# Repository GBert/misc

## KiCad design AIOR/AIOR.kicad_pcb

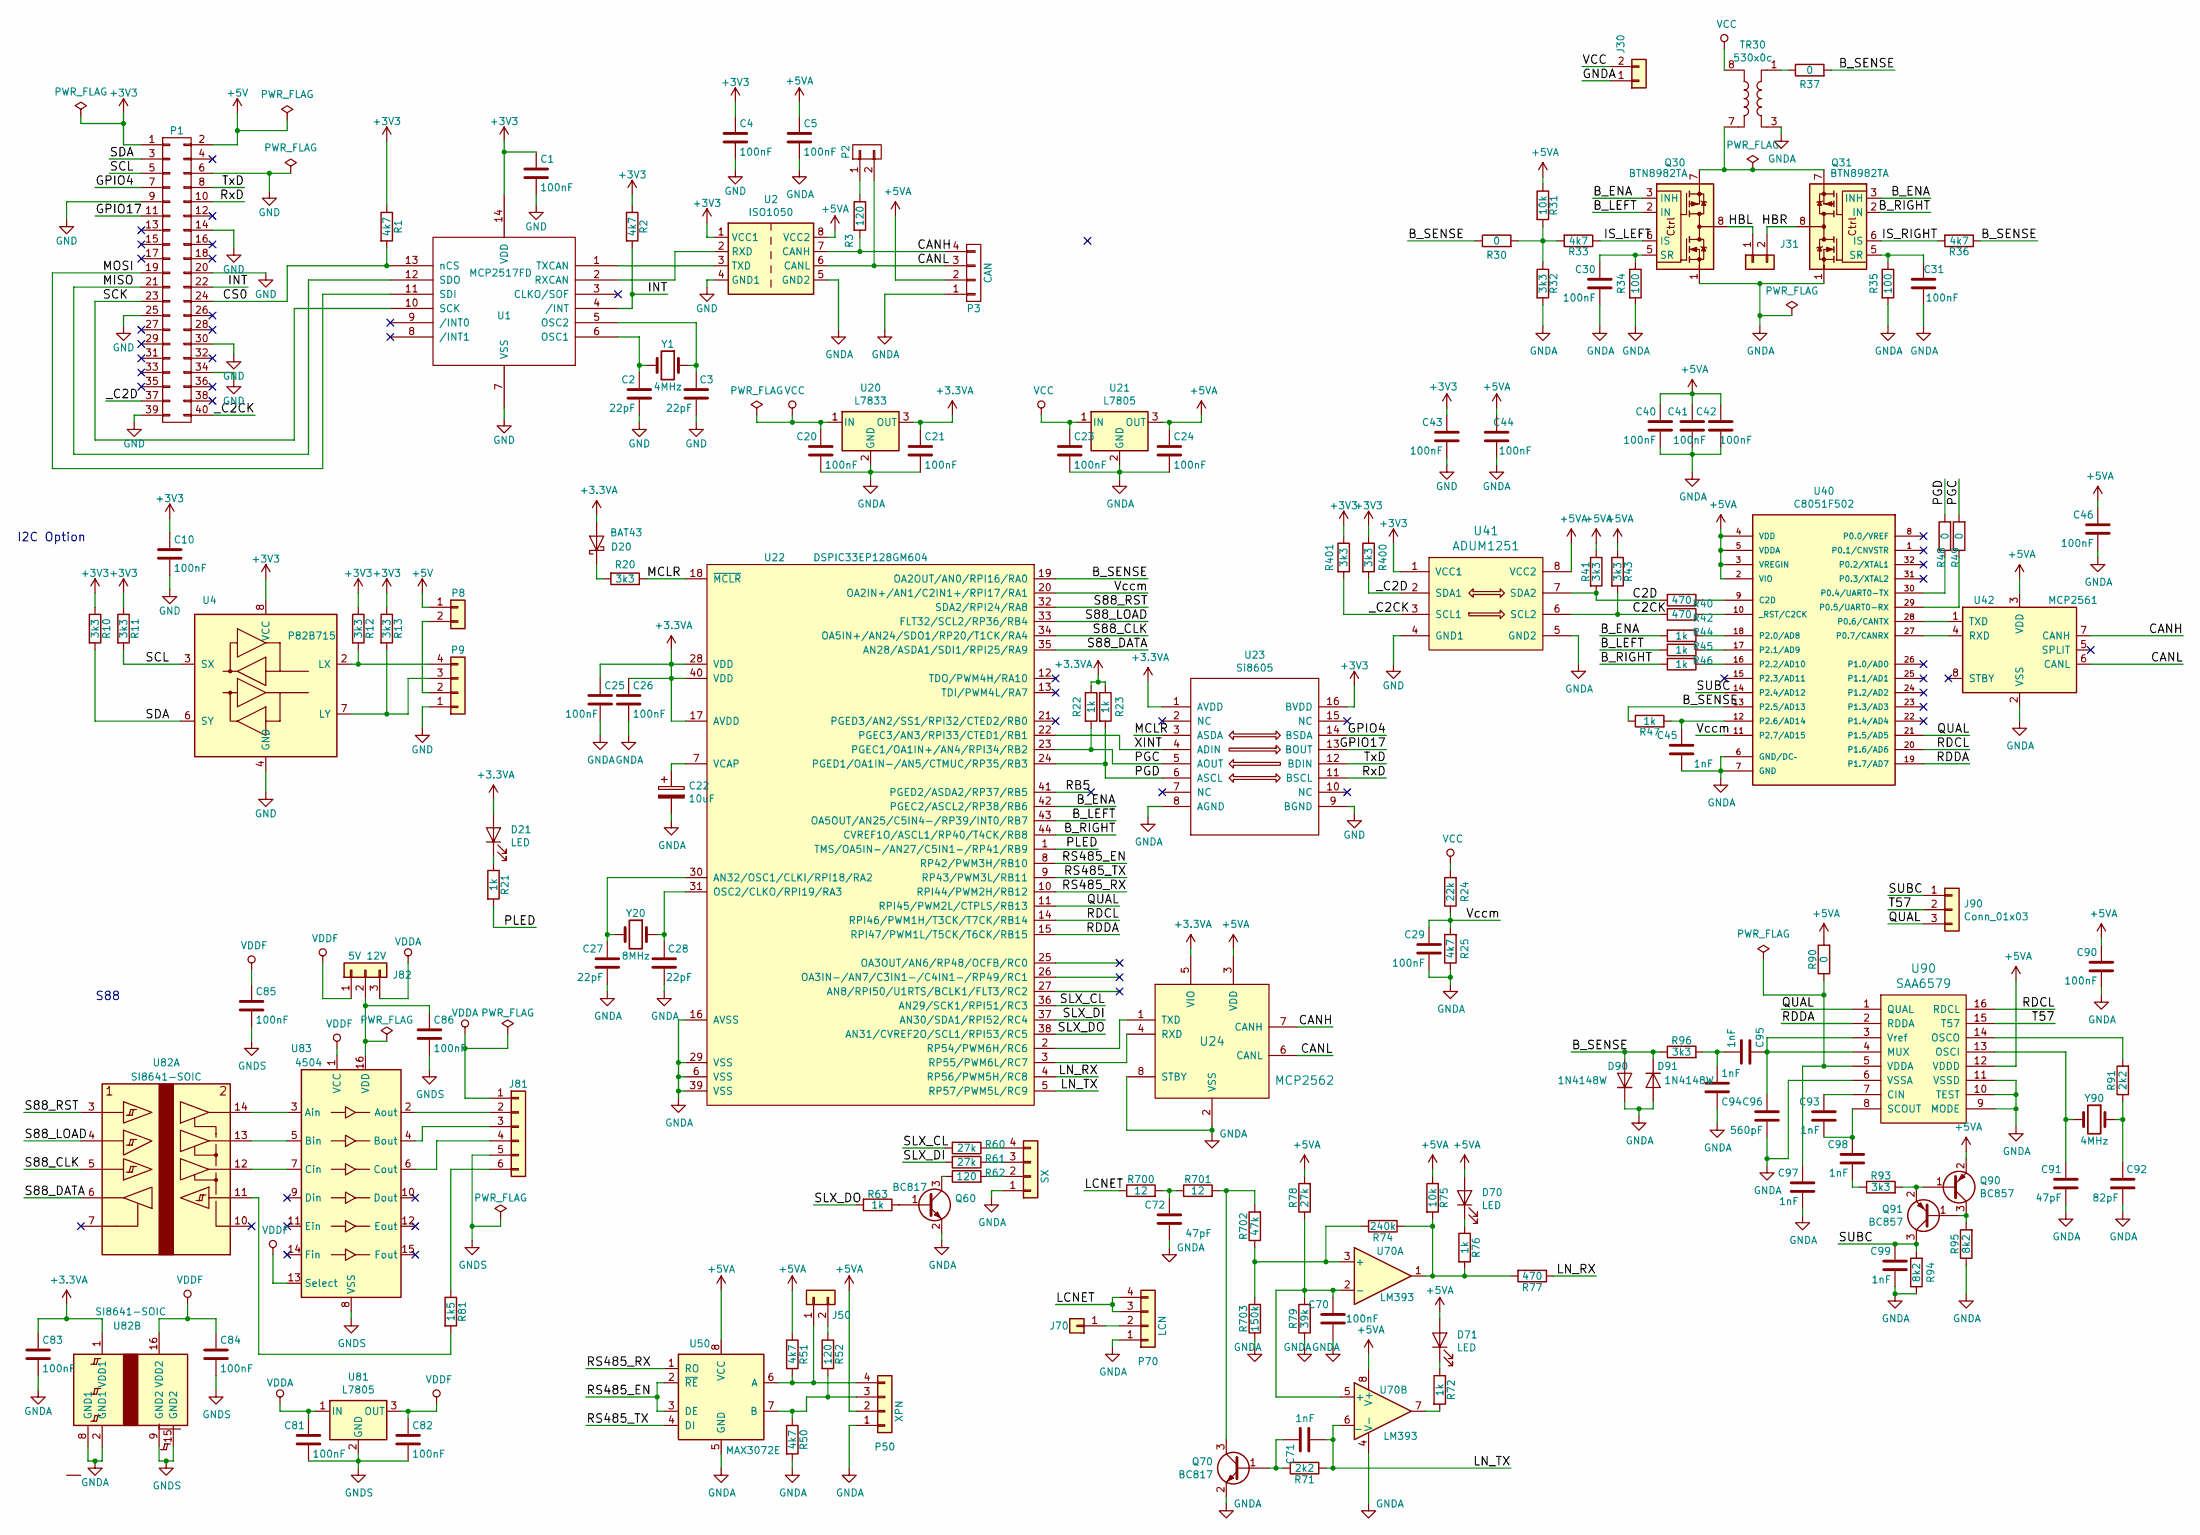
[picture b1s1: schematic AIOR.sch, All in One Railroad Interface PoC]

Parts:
C1, C4, C5, C10, C20, C21, C23, C24, C25, C26, C29, C30, C31, C40, C41, C42, C43, C44, C46, C70, C81, C82, C83, C84, C85, C86, C90: 100nF; C_0805_2012Metric_Pad1.15x1.40mm_HandSolder
C2, C3, C27, C28: 22pF; C_0805_2012Metric_Pad1.15x1.40mm_HandSolder
C22: 10uF; CP_EIA-6032-20_AVX-F_Pad2.25x2.35mm_HandSolder
C45, C71, C93, C94, C95, C97, C98, C99: 1nF; C_0805_2012Metric_Pad1.15x1.40mm_HandSolder
C72, C91: 47pF; C_0805_2012Metric_Pad1.15x1.40mm_HandSolder
C92: 82pF; C_0805_2012Metric_Pad1.15x1.40mm_HandSolder
C96: 560pF; C_0805_2012Metric_Pad1.15x1.40mm_HandSolder
D20: BAT43; D_SOD-323_HandSoldering
D21, D70, D71: LED; LED_0805_2012Metric_Pad1.15x1.40mm_HandSolder
D90, D91: 1N4148W; D_SOD-123
J30, J31: Conn_01x02; mkds_1,5-2
J50: Conn_01x02; PinHeader_1x02_P2.54mm_Vertical
J70: Conn_01x01; PinHeader_1x01_P2.54mm_Vertical
J81: S88; PinHeader_1x06_P2.54mm_Horizontal
J82: 5V 12V; PinHeader_1x03_P2.54mm_Vertical
J90: Conn_01x03; PinHeader_1x03_P2.54mm_Vertical
P1: CONN_02X20; Socket_Strip_Straight_2x20
P2: CONN_01X02; PinHeader_1x02_P2.54mm_Vertical
P3: CAN; b4b-ph-kl
P8: Conn_01x02; PinHeader_1x02_P2.54mm_Vertical
P9: Conn_01x04; s4b-ph-kl
P50: XPN; b4b-ph-kl
P60: SX; b4b-ph-kl
P70: LCN; b4b-ph-kl
Q30, Q31: BTN8982TA; TO-263-7_TabPin8
Q60, Q70: BC817; SOT-23_Handsoldering
Q90, Q91: BC857; SOT-23_Handsoldering
R1, R2, R25, R33, R36, R50, R51: 4k7; R_0805_2012Metric_Pad1.15x1.40mm_HandSolder
R3, R52: 120; R_1206_3216Metric_Pad1.42x1.75mm_HandSolder
R10, R11, R12, R13, R20, R32, R41, R43, R93, R96, R400, R401: 3k3; R_0805_2012Metric_Pad1.15x1.40mm_HandSolder
R21, R22, R23, R44, R45, R46, R47, R63, R72, R76: 1k; R_0805_2012Metric_Pad1.15x1.40mm_HandSolder
R24: 22k; R_0805_2012Metric_Pad1.15x1.40mm_HandSolder
R30, R37, R48, R49, R90: 0; R_0805_2012Metric_Pad1.15x1.40mm_HandSolder
R31, R75: 10k; R_0805_2012Metric_Pad1.15x1.40mm_HandSolder
R34, R35: 100; R_0805_2012Metric_Pad1.15x1.40mm_HandSolder
R40, R42, R77: 470; R_0805_2012Metric_Pad1.15x1.40mm_HandSolder
R60, R61, R78: 27k; R_0805_2012Metric_Pad1.15x1.40mm_HandSolder
R62: 120; R_0805_2012Metric_Pad1.15x1.40mm_HandSolder
R71, R91: 2k2; R_0805_2012Metric_Pad1.15x1.40mm_HandSolder
R74: 240k; R_0805_2012Metric_Pad1.15x1.40mm_HandSolder
R79: 39k; R_0805_2012Metric_Pad1.15x1.40mm_HandSolder
R81: 1k5; R_0805_2012Metric_Pad1.15x1.40mm_HandSolder
R94, R95: 8k2; R_0805_2012Metric_Pad1.15x1.40mm_HandSolder
R700, R701: 12; R_1206_3216Metric_Pad1.42x1.75mm_HandSolder
R702: 47k; R_0805_2012Metric_Pad1.15x1.40mm_HandSolder
R703: 150k; R_0805_2012Metric_Pad1.15x1.40mm_HandSolder
TR30: 530x0c; 530x0C
U1: MCP2517FD; so-14
U2: ISO1050; mdip_8
U4: P82B715; so-8
U20: L7833; TO-252-2
U21, U81: L7805; TO-252-2
U22: DSPIC33EP128GM604; LQFP-44_10x10mm_P0.8mm
U23: Si8605; so-16
U24: MCP2562; so-8
U40: C8051F502; LQFP-32_7x7mm_P0.8mm
U41: ADUM1251; so-8
U42: MCP2561; so-8
U50: MAX3072E; so-8
U70: LM393; so-8
U82: SI8641-SOIC; so-16
U83: 4504; so-16
U90: SAA6579; SOP-16_7.5x10.4mm_P1.27mm
Y1, Y90: 4MHz; crystal_hc-49s
Y20: 8MHz; crystal_hc-49s

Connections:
+3.3VA: C21.1, C25.1, C26.1, C83.1, D20.2 (A), D21.2 (A), R22.1, R23.1, U20.3 (OUT), U22.17 (AVDD), U22.28 (VDD), U22.40 (VDD), U23.1 (AVDD), U24.5 (VIO~), U82.1 (VDD1)
+3V3: C1.1, C4.1, C10.1, C43.1, P1.1, R1.1, R2.1, R10.1, R11.1, R12.1, R13.1, R400.1, R401.1, U1.14 (VDD), U2.1 (VCC1), U4.8 (VCC), U23.16 (BVDD), U41.1 (VCC1)
+5V: P1.2, P8.1
+5VA: C5.1, C24.1, C40.1, C41.1, C42.1, C44.1, C46.1, C90.1, D70.2 (A), D71.2 (A), P3.2, P50.2, Q90.2 (E), R31.1, R41.1, R43.1, R51.1, R75.1, R78.2, R90.2, U2.8 (VCC2), U21.3 (OUT), U24.3 (VDD~), U40.2 (VIO), U40.3 (VREGIN), U40.4 (VDD), U40.5 (VDDA), U41.8 (VCC2), U42.3 (VDD), U50.8 (VCC), U70.8 (V+), U90.12 (VDDD)
/B_ENA: Q30.3 (INH), Q31.3 (INH), R44.2, U22.42 (PGEC2/ASCL2/RP38/RB6)
/B_LEFT: Q30.2 (IN), R45.2, U22.43 (OA5OUT/AN25/C5IN4-/RP39/INT0/RB7)
/B_RIGHT: Q31.2 (IN), R46.2, U22.44 (CVREF1O/ASCL1/RP40/T4CK/RB8)
/B_SENSE: D90.2 (A), D91.1 (K), R30.1, R36.1, R37.2, R47.1, R96.1, U22.19 (OA2OUT/AN0/RPI16/RA0), U40.13 (P2.5/AD13)
/C2CK: R42.2, R43.2, U41.6 (SCL2)
/C2D: R40.2, R41.2, U41.7 (SDA2)
/CANH: P3.4, R3.2, U2.7 (CANH), U24.7 (CANH), U42.7 (CANH)
/CANL: P2.2, P3.3, U2.6 (CANL), U24.6 (CANL), U42.6 (CANL)
/CS0: P1.24, R1.2, U1.13 (nCS)
/GPIO4: P1.7, U23.14 (BSDA)
/GPIO17: P1.11, U23.13 (BOUT)
/HBL: J31.1, Q30.4, Q30.8
/HBR: J31.2, Q31.4, Q31.8
/INT: P1.22, R2.2, U1.4 (/INT)
/IS_LEFT: Q30.6 (IS), R33.1
/IS_RIGHT: Q31.6 (IS), R36.2
/LCNET: P70.3, P70.4, R700.1
/LN_RX: R77.1, U22.4 (RP56/PWM5H/RC8)
/LN_TX: C71.2, R71.1, U22.5 (RP57/PWM5L/RC9), U70.6 (_)
/MCLR: R20.1, U22.18 (~MCLR), U23.3 (ASDA)
/MISO: P1.21, U1.12 (SDO)
/MOSI: P1.19, U1.11 (SDI)
/PGC: R22.2, R49.2, U22.23 (PGEC1/OA1IN+/AN4/RPI34/RB2), U23.5 (AOUT)
/PGD: R23.2, R48.2, U22.24 (PGED1/OA1IN-/AN5/CTMUC/RP35/RB3), U23.6 (ASCL)
/PLED: R21.2, U22.1 (TMS/OA5IN-/AN27/C5IN1-/RP41/RB9)
/QUAL: J90.3, U22.11 (RPI45/PWM2L/CTPLS/RB13), U40.21 (P1.5/AD5), U90.1 (QUAL)
/RB5: U22.41 (PGED2/ASDA2/RP37/RB5)
/RDCL: U22.14 (RPI46/PWM1H/T3CK/T7CK/RB14), U40.20 (P1.6/AD6), U90.16 (RDCL)
/RDDA: U22.15 (RPI47/PWM1L/T5CK/T6CK/RB15), U40.19 (P1.7/AD7), U90.2 (RDDA)
/RS485_EN: U22.8 (RP42/PWM3H/RB10), U50.2 (~RE~), U50.3 (DE)
/RS485_RX: U22.10 (RPI44/PWM2H/RB12), U50.1 (RO)
/RS485_TX: U22.9 (RP43/PWM3L/RB11), U50.4 (DI)
/RxD: P1.10, U23.11 (BSCL)
/S88_CLK: U22.34 (OA5IN+/AN24/SDO1/RP20/T1CK/RA4), U82.5
/S88_DATA: U22.35 (AN28/ASDA1/SDI1/RPI25/RA9), U82.6
/S88_LOAD: U22.33 (FLT32/SCL2/RP36/RB4), U82.4
/S88_RST: U22.32 (SDA2/RPI24/RA8), U82.3
/SCK: P1.23, U1.10 (SCK)
/SCL: P1.5, R11.2, U4.3 (SX)
/SDA: P1.3, R10.2, U4.6 (SY)
/SLX_CL: R60.2, U22.36 (AN29/SCK1/RPI51/RC3)
/SLX_DI: R61.2, U22.37 (AN30/SDA1/RPI52/RC4)
/SLX_DO: R63.2, U22.38 (AN31/CVREF2O/SCL1/RPI53/RC5)
/SUBC: C99.1, J90.1, Q91.3 (C), R94.2, U40.14 (P2.4/AD12)
/T57: J90.2, U90.15 (T57)
/TxD: P1.8, U23.12 (BDIN)
/Vccm: C29.1, R24.1, R25.2, U22.20 (OA2IN+/AN1/C2IN1+/RPI17/RA1), U40.11 (P2.7/AD15)
/XINT: U22.22 (PGEC3/AN3/RPI33/CTED1/RB1), U23.4 (ADIN)
/_C2CK: P1.40, R401.2, U41.3 (SCL1)
/_C2D: P1.37, R400.2, U41.2 (SDA1)
GND: C1.2, C2.2, C3.2, C4.2, C10.2, C43.2, P1.6, P1.9, P1.14, P1.20, P1.25, P1.30, P1.34, P1.39, P9.1, U1.7 (VSS), U2.4 (GND1), U4.4 (GND), U23.9 (BGND), U41.4 (GND1)
GNDA: C5.2, C20.2, C21.2, C22.2, C23.2, C24.2, C25.2, C26.2, C27.2, C28.2, C29.2, C30.2, C31.2, C40.2, C41.2, C42.2, C44.2, C45.2, C46.2, C70.2, C72.2, C83.2, C90.2, C91.2, C92.2, C94.1, C96.2, C97.2, C99.2, D90.1 (K), D91.2 (A), J30.1, P3.1, P50.1, P60.1, P70.1, Q30.1, Q31.1, Q60.2 (E), Q70.2 (E), R25.1, R32.2, R34.2, R35.2, R50.2, R79.1, R94.1, R95.1, R703.1, TR30.3, U2.5 (GND2), U20.2 (GND), U21.2 (GND), U22.6 (VSS), U22.16 (AVSS), U22.29 (VSS), U22.39 (VSS), U23.8 (AGND), U24.2 (VSS~), U24.8 (STBY), U40.6 (GND/DC–), U40.7 (GND), U41.5 (GND2), U42.2 (VSS), U50.5 (GND), U70.4 (V-), U82.2 (GND1), U82.8 (GND1), U90.6 (VSSA), U90.9 (MODE), U90.10 (TEST), U90.11 (VSSD)
GNDS: C81.2, C82.2, C84.2, C85.2, C86.2, J81.5, U81.2 (GND), U82.9 (GND2), U82.15 (GND2), U83.8 (VSS)
unnamed: C2.1, U1.6 (OSC1), Y1.2
unnamed: C3.1, U1.5 (OSC2), Y1.1
unnamed: C22.1, U22.7 (VCAP)
unnamed: C27.1, U22.30 (AN32/OSC1/CLKI/RPI18/RA2), Y20.2
unnamed: C28.1, U22.31 (OSC2/CLKO/RPI19/RA3), Y20.1
unnamed: C30.1, Q30.5 (SR), R34.1
unnamed: C31.1, Q31.5 (SR), R35.1
unnamed: C45.1, R47.2, U40.12 (P2.6/AD14)
unnamed: C70.1, R78.1, R79.2, U70.2 (-), U70.5 (+)
unnamed: C71.1, Q70.1 (B), R71.2
unnamed: C72.1, R700.2, R701.1
unnamed: C86.1, J82.2, U83.16 (VDD)
unnamed: C91.1, U90.13 (OSCI), Y90.2
unnamed: C92.1, R91.1, Y90.1
unnamed: C93.1, U90.7 (CIN)
unnamed: C93.2, C98.1, U90.8 (SCOUT)
unnamed: C94.2, C95.2, R96.2
unnamed: C95.1, C96.1, U90.3 (Vref), U90.4 (MUX)
unnamed: C97.1, R90.1, U90.5 (VDDA)
unnamed: C98.2, R93.1
unnamed: D20.1 (K), R20.2
unnamed: D21.1 (K), R21.1
unnamed: D70.1 (K), R76.1
unnamed: D71.1 (K), R72.1
unnamed: J50.1, P50.4, R51.2, U50.6 (A)
unnamed: J50.2, R52.1
unnamed: J70.1, P70.2
unnamed: J81.2, U83.2 (Aout)
unnamed: J81.3, U83.4 (Bout)
unnamed: J81.4, U83.6 (Cout)
unnamed: J81.6, R81.1
unnamed: P2.1, R3.1
unnamed: P8.2, P9.2
unnamed: P9.3, R13.2, U4.7 (LY)
unnamed: P9.4, R12.2, U4.2 (LX)
unnamed: P50.3, R50.1, R52.2, U50.7 (B)
unnamed: P60.2, R62.2
unnamed: P60.3, R61.1
unnamed: P60.4, R60.1
unnamed: Q30.7, Q31.7, TR30.7
unnamed: Q60.1 (B), R63.1
unnamed: Q60.3 (C), R62.1
unnamed: Q70.3 (C), R701.2, R702.2
unnamed: Q90.1 (B), Q91.2 (E), R93.2
unnamed: Q90.3 (C), Q91.1 (B), R95.2
unnamed: R30.2, R31.2, R32.1, R33.2
unnamed: R37.1, TR30.1
unnamed: R40.1, U40.9 (C2D)
unnamed: R42.1, U40.10 (_RST/C2CK)
unnamed: R44.1, U40.18 (P2.0/AD8)
unnamed: R45.1, U40.17 (P2.1/AD9)
unnamed: R46.1, U40.16 (P2.2/AD10)
unnamed: R48.1, U40.30 (P0.4/UART0-TX)
unnamed: R49.1, U40.29 (P0.5/UART0-RX)
unnamed: R72.2, U70.7
unnamed: R74.1, R75.2, R76.2, R77.2, U70.1
unnamed: R81.2, U82.11
unnamed: R91.2, U90.14 (OSCO)
unnamed: R74.2, R702.1, R703.2, U70.3 (+)
unnamed: U1.1 (TXCAN), U2.3 (TXD)
unnamed: U1.2 (RXCAN), U2.2 (RXD)
unnamed: U22.2 (RP54/PWM6H/RC6), U24.1 (TXD)
unnamed: U22.3 (RP55/PWM6L/RC7), U24.4 (RXD)
unnamed: U40.27 (P0.7/CANRX), U42.4 (RXD)
unnamed: U40.28 (P0.6/CANTX), U42.1 (TXD)
unnamed: U82.12, U83.7 (Cin)
unnamed: U82.13, U83.5 (Bin)
unnamed: U82.14, U83.3 (Ain)
VCC: C20.1, C23.1, J30.2, R24.2, TR30.8, U20.1 (IN), U21.1 (IN)
VDDA: C81.1, J81.1, J82.3, U81.1 (IN)
VDDF: C82.1, C84.1, C85.1, J82.1, U81.3 (OUT), U82.16 (VDD2), U83.1 (VCC), U83.13 (Select)

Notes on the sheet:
I2C Option
S88

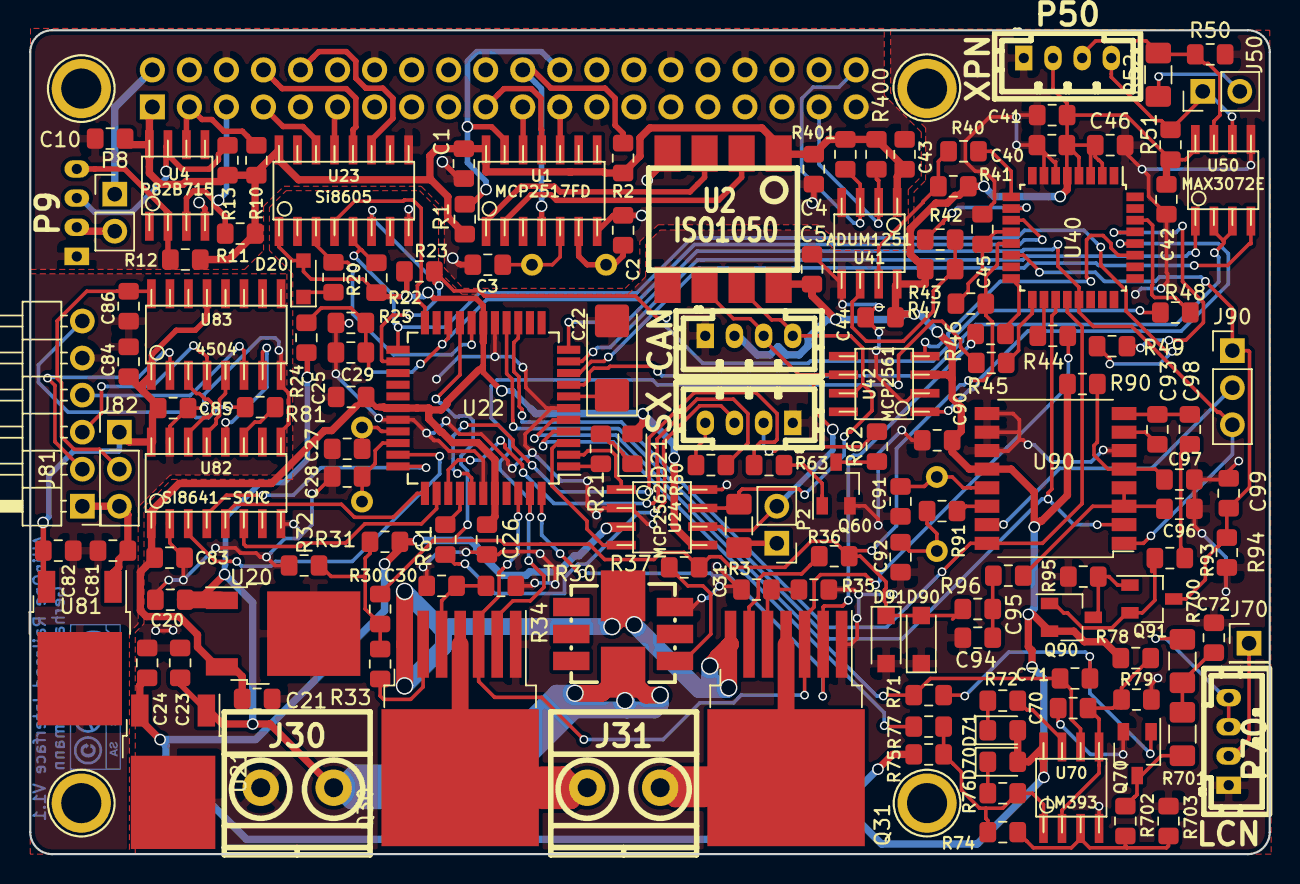
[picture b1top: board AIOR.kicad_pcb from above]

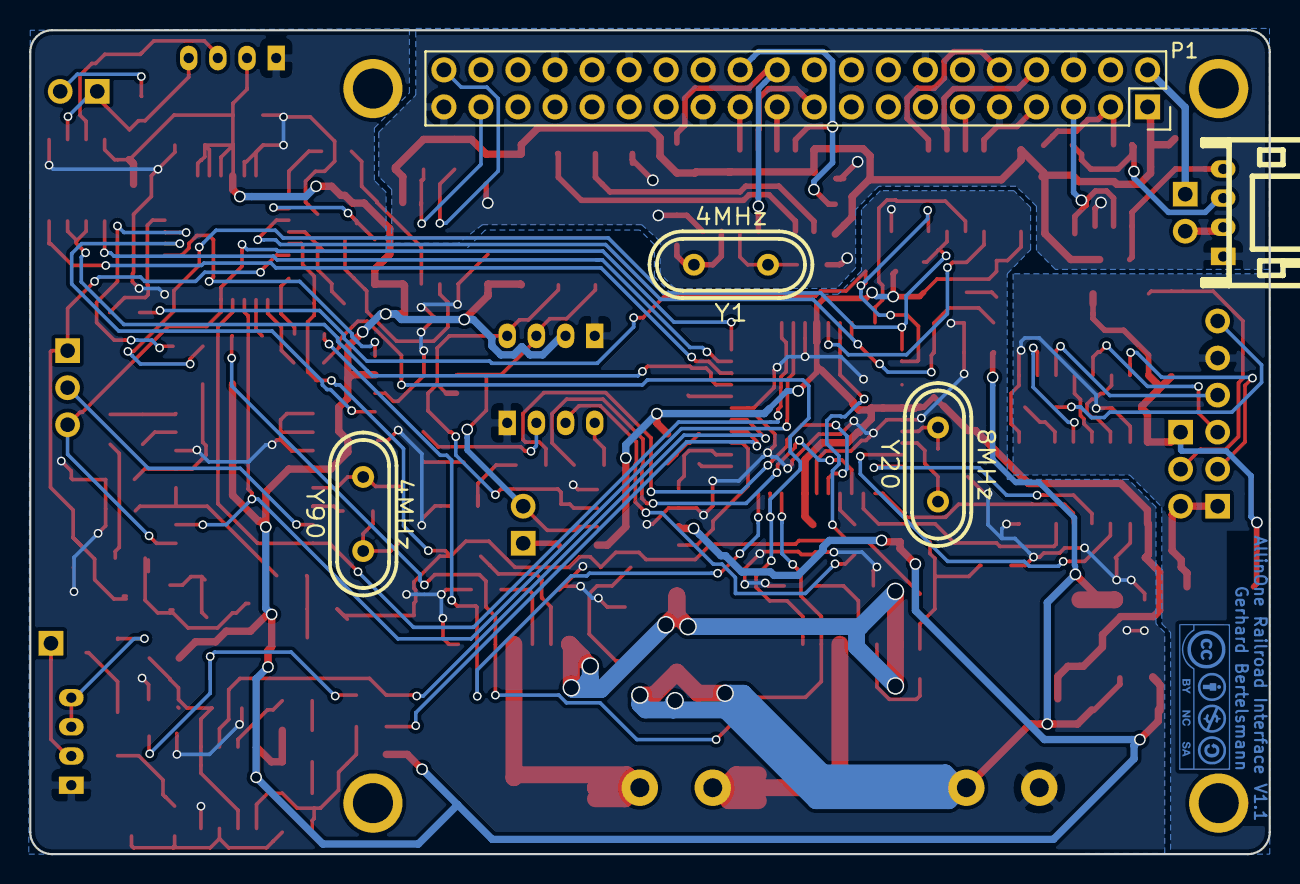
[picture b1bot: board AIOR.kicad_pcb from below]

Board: 2 copper layers, 85.0 x 56.5 mm, 151 parts (5 on the bottom side), 127 nets.

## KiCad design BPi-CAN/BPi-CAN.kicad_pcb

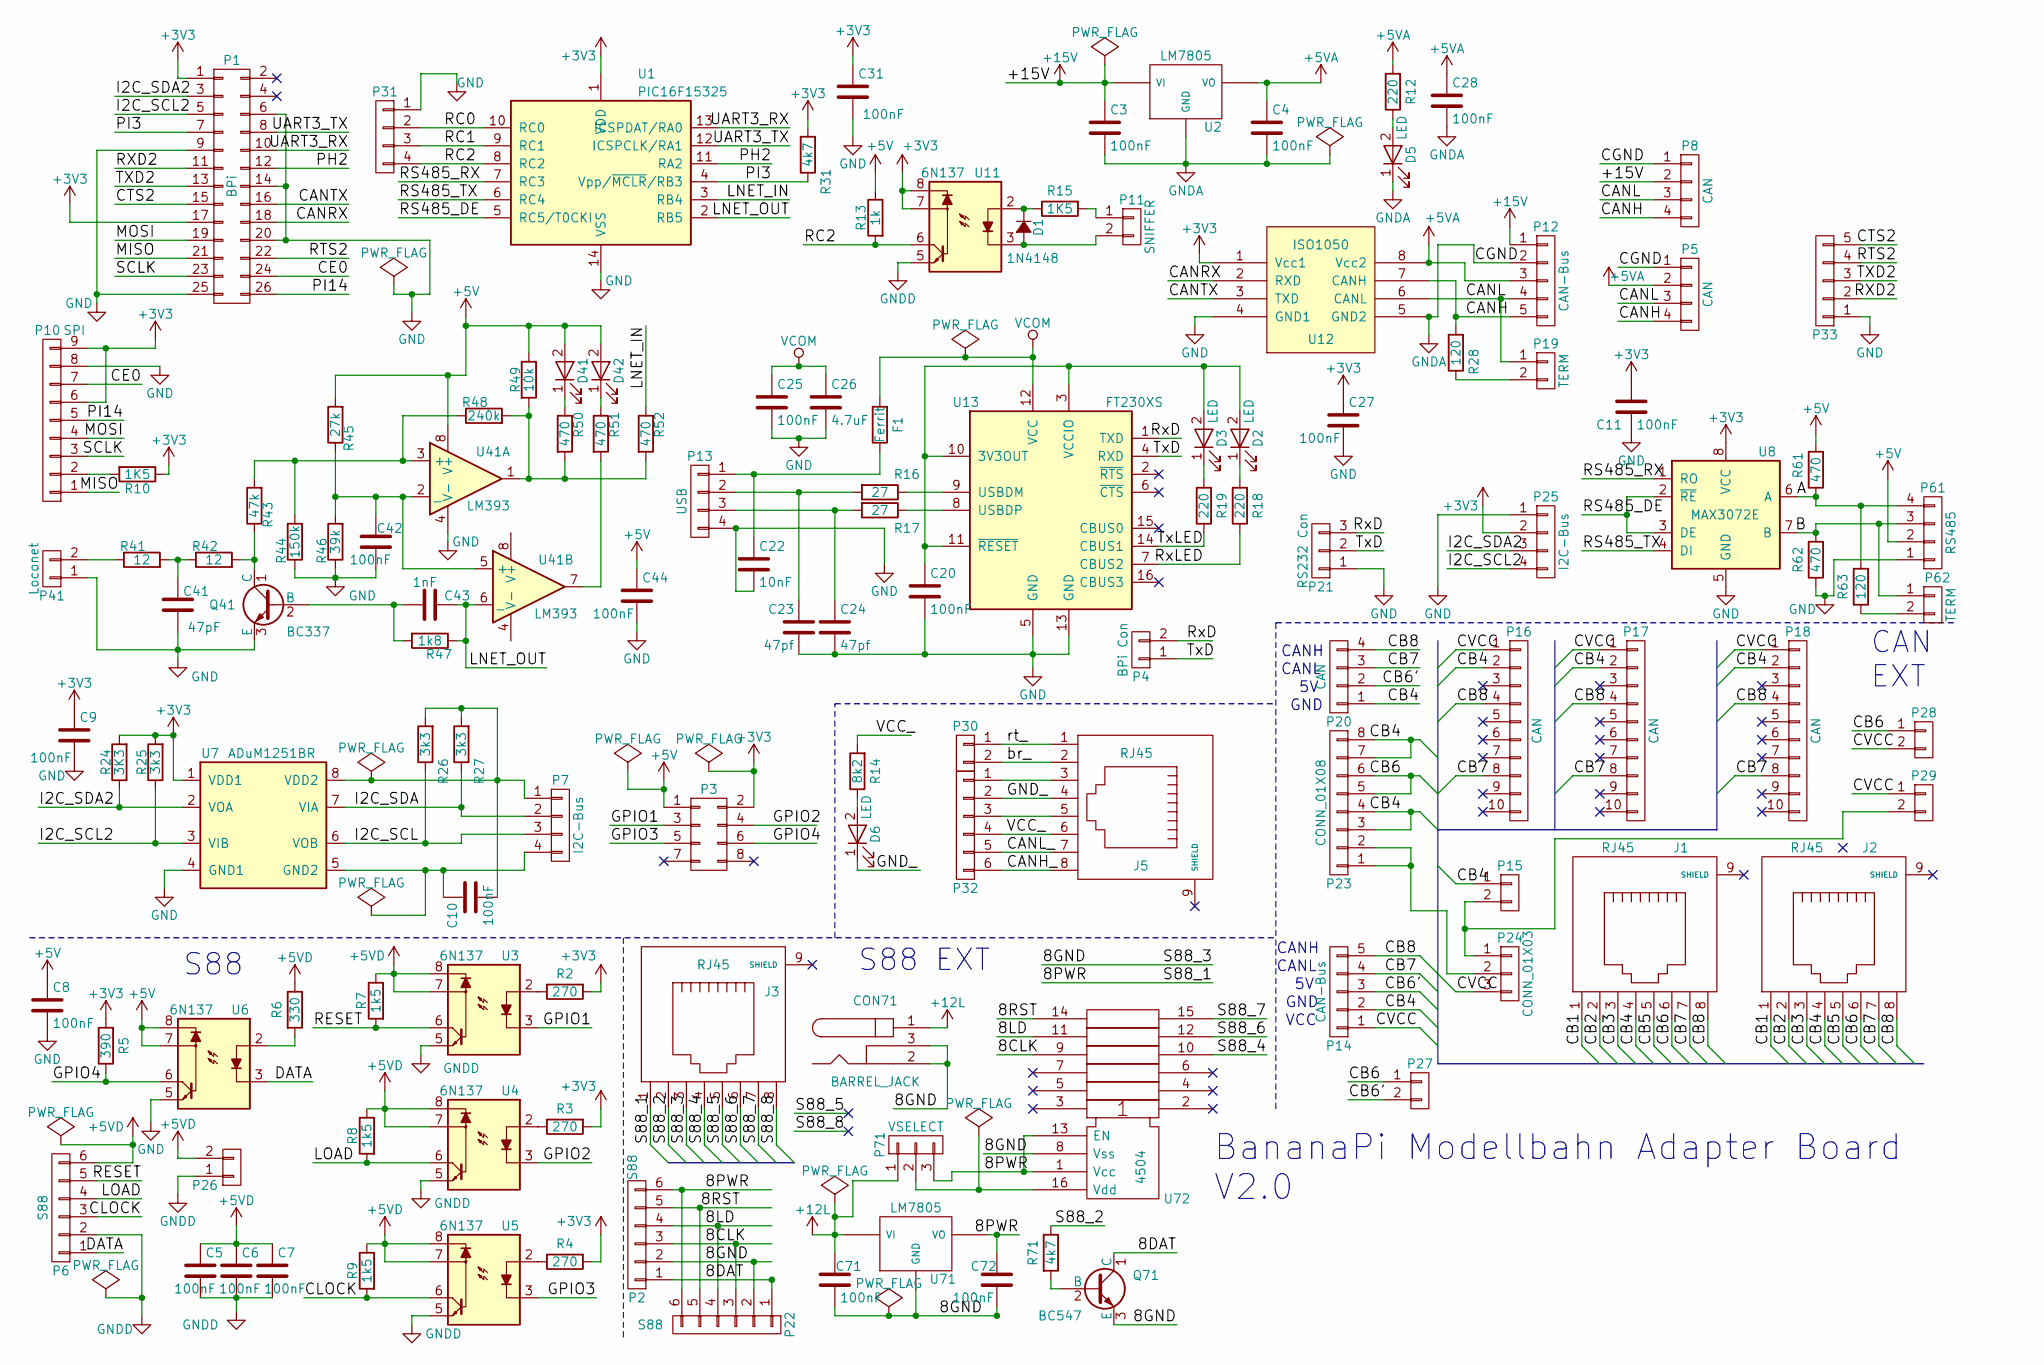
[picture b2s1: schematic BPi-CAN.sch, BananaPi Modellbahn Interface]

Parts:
C3, C4, C5, C6, C7, C8, C11, C71, C72: 100nF; C_Disc_D3_P2.5
C9, C10, C20, C25: 100nF; R_0805_HandSoldering_II
C22: 10nF; R_0805_HandSoldering_II
C23, C24: 47pf; R_0805_HandSoldering_II
C26: 4.7uF; R_0805_HandSoldering_II
C27, C28, C31, C42, C44: 100nF; cnp_3mm_disc
C41: 47pF; cnp_3mm_disc
C43: 1nF; cnp_3mm_disc
CON71: BARREL_JACK
D1: 1N4148; diode_do35
D2, D3: LED; LED-0805
D5, D6, D41, D42: LED; LED-3MM
F1: Ferrit; R_0805_HandSoldering_II
J1, J2, J3, J5: RJ45; megb8-8
P1: BPi; Socket_Strip_Straight_2x13
P2, P6, P22: S88; Pin_Header_Straight_1x06
P3: CONN_02X04; Socket_Strip_Straight_2x04
P4: BPi Con; Socket_Strip_Straight_1x02
P5, P20: CAN; b4b-ph-kl
P7: I2C-Bus; Pin_Header_Straight_1x04
P8: CAN; pt_1,5-4-3,5-h
P10: SPI; Pin_Header_Straight_1x09
P11: SNIFFER; pt_1,5-2-3,5-h
P12, P14: CAN-Bus; pt_1,5-5-3,5-h
P13: USB; conn_usb_B
P15: POWER; pt_1,5-2-3,5-h
P16, P17, P18: CAN; minidin-10
P19, P62: TERM; Pin_Header_Straight_1x02
P21: RS232 Con; Pin_Header_Straight_1x03
P23: CONN_01X08; DCDC
P24: CONN_01X03; Pin_Header_Straight_1x03
P25: I2C-Bus; Connectors_JST_S4B-PH-K
P26, P30: CONN_01X02; Pin_Header_Straight_1x02
P27, P28, P29: POWER; Pin_Header_Straight_1x02
P31: CONN_01X04; Pin_Header_Straight_1x04
P32: CONN_01X06; Pin_Header_Straight_1x06
P33: CONN_01X05; Pin_Header_Straight_1x05
P41: Loconet; Pin_Header_Straight_1x02
P61: RS485; b4b-ph-kl
P71: VSELECT; Pin_Header_Straight_1x03
Q41: BC337; TO-92_Inline_Narrow_Oval
Q71: BC547; TO-92_Inline_Narrow_Oval
R2, R3, R4: 270; RC03
R5: 390; RC03
R6: 330; RC03
R7, R8, R9: 1k5; RC03
R10, R15: 1K5; RC03
R12: 220; RC03
R13: 1k; RC03
R14: 8k2; RC03
R16, R17: 27; R_0805_HandSoldering_II
R18, R19: 220; R_0805_HandSoldering_II
R24: 3K3; R_0805_HandSoldering_II
R25, R26, R27: 3k3; R_0805_HandSoldering_II
R28, R63: 120; RC03
R31, R71: 4k7; RC03
R41, R42: 12; RC03
R43: 47k; RC03
R44: 150k; RC03
R45: 27k; RC03
R46: 39k; RC03
R47: 1k8; RC03
R48: 240k; RC03
R49: 10k; RC03
R50, R51, R52, R61, R62: 470; RC03
U1: PIC16F15325; dil_14-300_socket
U2: LM7805; TO-220-78xx
U3, U4, U5, U6, U11: 6N137; dil_8-300_socket
U7: ADuM1251BR; SOIC-8_3.9x4.9mm_Pitch1.27mm
U8: MAX3072E; dil_8-300_socket
U12: ISO1050; mdip_8
U13: FT230XS; ssop-16
U41: LM393; dil_8-300_socket
U71: LM7805; TO-220_Neutral123_Vertical
U72: 4504; dil_16-300_socket

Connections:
+3V3: C9.1, C11.1, C27.1, C31.1, P1.1, P1.17, P3.2, P10.6, P10.9, P25.2, R2.2, R3.2, R4.2, R5.2, R10.1, R24.2, R25.2, R31.2, U1.1 (VDD), U7.1 (VDD1), U8.8 (VCC), U11.7, U11.8, U12.1 (Vcc1)
+5V: C8.1, C44.1, D41.2 (A), D42.2 (A), P3.1, P61.2, R13.1, R45.2, R49.1, R61.2, U6.7, U6.8, U41.8 (V+)
+5VA: C4.1, C28.1, P5.2, P12.3, R12.2, U2.VO, U12.8 (Vcc2)
+5VD: C5.1, C6.1, C7.1, P6.6, P26.2, R6.1, R7.1, R8.1, R9.1, U3.7, U3.8, U4.7, U4.8, U5.7, U5.8
+12L: C71.1, CON71.1, P71.1, U71.VI
+15V: C3.1, P8.2, P12.1, U2.VI
/8CLK: P2.3, P22.3, U72.9
/8DAT: P2.1, P22.1, Q71.1 (C)
/8GND: C71.2, C72.2, CON71.2, CON71.3, J3.3, P2.2, P22.2, Q71.3 (E), U71.GND, U72.8 (Vss)
/8LD: P2.4, P22.4, U72.11
/8PWR: C72.1, J3.1, P2.6, P22.6, P71.3, U71.VO, U72.1 (Vcc), U72.13 (EN)
/8RST: P2.5, P22.5, U72.14
/A: P61.4, R61.1, R63.2, U8.6 (A)
/B: P61.3, P62.1, R62.2, U8.7 (B)
/CANH: P5.4, P8.4, P12.5, R28.2, U12.7 (CANH)
/CANH_: J5.8, P32.6
/CANL: P5.3, P8.3, P12.4, P19.1, U12.6 (CANL)
/CANL_: J5.7, P32.5
/CANRX: P1.18, U12.2 (RXD)
/CANTX: P1.16, U12.3 (TXD)
/CB1: J1.1, J2.1
/CB2: J1.2, J2.2
/CB3: J1.3, J2.3
/CB4: J1.4, J2.4, P14.2, P15.1, P16.2, P17.2, P18.2, P20.1, P23.3, P23.4, P23.7, P23.8
/CB5: J1.5, J2.5
/CB6: J1.6, J2.6, P23.5, P23.6, P27.1, P28.1
/CB6': P14.3, P20.2, P27.2
/CB7: J1.7, J2.7, P14.4, P16.8, P17.8, P18.8, P20.3
/CB8: J1.8, J2.8, P14.5, P16.4, P17.4, P18.4, P20.4
/CE0: P1.24, P10.7
/CLOCK: P6.3, R9.2, U5.6
/CTS2: P1.15, P33.5
/CVCC: P14.1, P16.1, P17.1, P18.1, P24.3, P28.2, P29.1
/DATA: P6.1, U6.3
/GND_: D6.1 (K), J5.4, P32.2
/GPIO1: P3.3, U3.3
/GPIO2: P3.4, U4.3
/GPIO3: P3.5, U5.3
/GPIO4: P3.6, R5.1, U6.6
/I2C_SCL: P7.3, R26.1, U7.6 (VOB)
/I2C_SCL2: P1.5, P25.4, R25.1, U7.3 (VIB)
/I2C_SDA: P7.2, R27.1, U7.7 (VIA)
/I2C_SDA2: P1.3, P25.3, R24.1, U7.2 (VOA)
/LNET_IN: R52.1, U1.3 (RB4)
/LNET_OUT: C43.1, R47.1, U1.2 (RB5), U41.6 (_)
/LOAD: P6.4, R8.2, U4.6
/MISO: P1.21, P10.1
/MOSI: P1.19, P10.4
/PH2: P1.12, U1.11 (RA2)
/PI3: P1.7, R31.1, U1.4 (Vpp/~MCLR~/RB3)
/PI14: P1.26, P10.5
/RC0: P31.2, U1.10 (RC0)
/RC1: P31.3, U1.9 (RC1)
/RC2: P31.4, R13.2, U1.8 (RC2), U11.6
/RESET: P6.5, R7.2, U3.6
/RS485_DE: U1.5 (RC5/T0CKI), U8.2 (~RE~), U8.3 (DE)
/RS485_RX: U1.7 (RC3), U8.1 (RO)
/RS485_TX: U1.6 (RC4), U8.4 (DI)
/RTS2: P1.22, P33.4
/RXD2: P1.11, P33.2
/RxD: P4.2, P21.3, U13.1 (TXD)
/RxLED: R18.1, U13.7 (CBUS2)
/S88_2: J3.2, R71.1
/S88_4: J3.4, U72.10
/S88_5: J3.5
/S88_6: J3.6, U72.12
/S88_7: J3.7, U72.15
/S88_8: J3.8
/SCLK: P1.23, P10.3
/TXD2: P1.13, P33.3
/TxD: P4.1, P21.2, U13.4 (RXD)
/TxLED: R19.1, U13.14 (CBUS1)
/UART3_RX: P1.10, U1.13 (ICSPDAT/RA0)
/UART3_TX: P1.8, U1.12 (ICSPCLK/RA1)
/VCC_: J5.6, P32.4, R14.2
/br_: J5.2, P30.2
/rt_: J5.1, P30.1
GND: C8.2, C9.2, C11.2, C20.2, C22.2, C23.2, C24.2, C25.2, C26.2, C27.2, C31.2, C41.2, C42.2, C44.2, P1.6, P1.9, P1.14, P1.20, P1.25, P10.8, P13.4, P21.1, P25.1, P31.1, P33.1, P41.1, P61.1, Q41.3 (E), R44.1, R46.1, R62.1, U1.14 (VSS), U6.5, U7.4 (GND1), U8.5 (GND), U12.4 (GND1), U13.5 (GND), U13.13 (GND), U41.4 (V-)
GNDA: C3.2, C4.2, C28.2, D5.1 (K), P5.1, P8.1, P12.2, U2.GND, U12.5 (GND2)
GNDD: C5.2, C6.2, C7.2, P6.2, P26.1, U3.5, U4.5, U5.5, U11.5
unnamed: C10.1, P7.1, R26.2, R27.2, U7.8 (VDD2)
unnamed: C10.2, P7.4, U7.5 (GND2)
unnamed: C20.1, D2.2 (A), D3.2 (A), U13.3 (VCCIO), U13.10 (3V3OUT), U13.11 (~RESET)
unnamed: C22.1, F1.1, P13.1
unnamed: C23.1, P13.2, R16.2
unnamed: C24.1, P13.3, R17.2
unnamed: C41.1, R41.2, R42.1
unnamed: C42.1, R45.1, R46.2, U41.2 (_), U41.5 (+)
unnamed: C43.2, Q41.2 (B), R47.2
unnamed: D1.1 (K), R15.1, U11.2
unnamed: D1.2 (A), P11.2, U11.3
unnamed: D2.1 (K), R18.2
unnamed: D3.1 (K), R19.2
unnamed: D5.2 (A), R12.1
unnamed: D6.2 (A), R14.1
unnamed: D41.1 (K), R50.1
unnamed: D42.1 (K), R51.1
unnamed: J5.3, P32.1
unnamed: J5.5, P32.3
unnamed: P10.2, R10.2
unnamed: P11.1, R15.2
unnamed: P15.2, P24.1, P29.2
unnamed: P19.2, R28.1
unnamed: P23.1, P23.2, P24.2
unnamed: P41.2, R41.1
unnamed: P62.2, R63.1
unnamed: P71.2, U72.16 (Vdd)
unnamed: Q41.1 (C), R42.2, R43.1
unnamed: Q71.2 (B), R71.2
unnamed: R2.1, U3.2
unnamed: R3.1, U4.2
unnamed: R4.1, U5.2
unnamed: R6.2, U6.2
unnamed: R16.1, U13.9 (USBDM)
unnamed: R17.1, U13.8 (USBDP)
unnamed: R43.2, R44.2, R48.1, U41.3 (+)
unnamed: R48.2, R49.2, R50.2, R52.2, U41.1
unnamed: R51.2, U41.7
VCOM: C25.1, C26.1, F1.2, U13.12 (VCC)

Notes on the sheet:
CANH
CANL
GND
VCC
BananaPi Modellbahn Adapter Board V2.0
S88
CAN EXT
S88 EXT

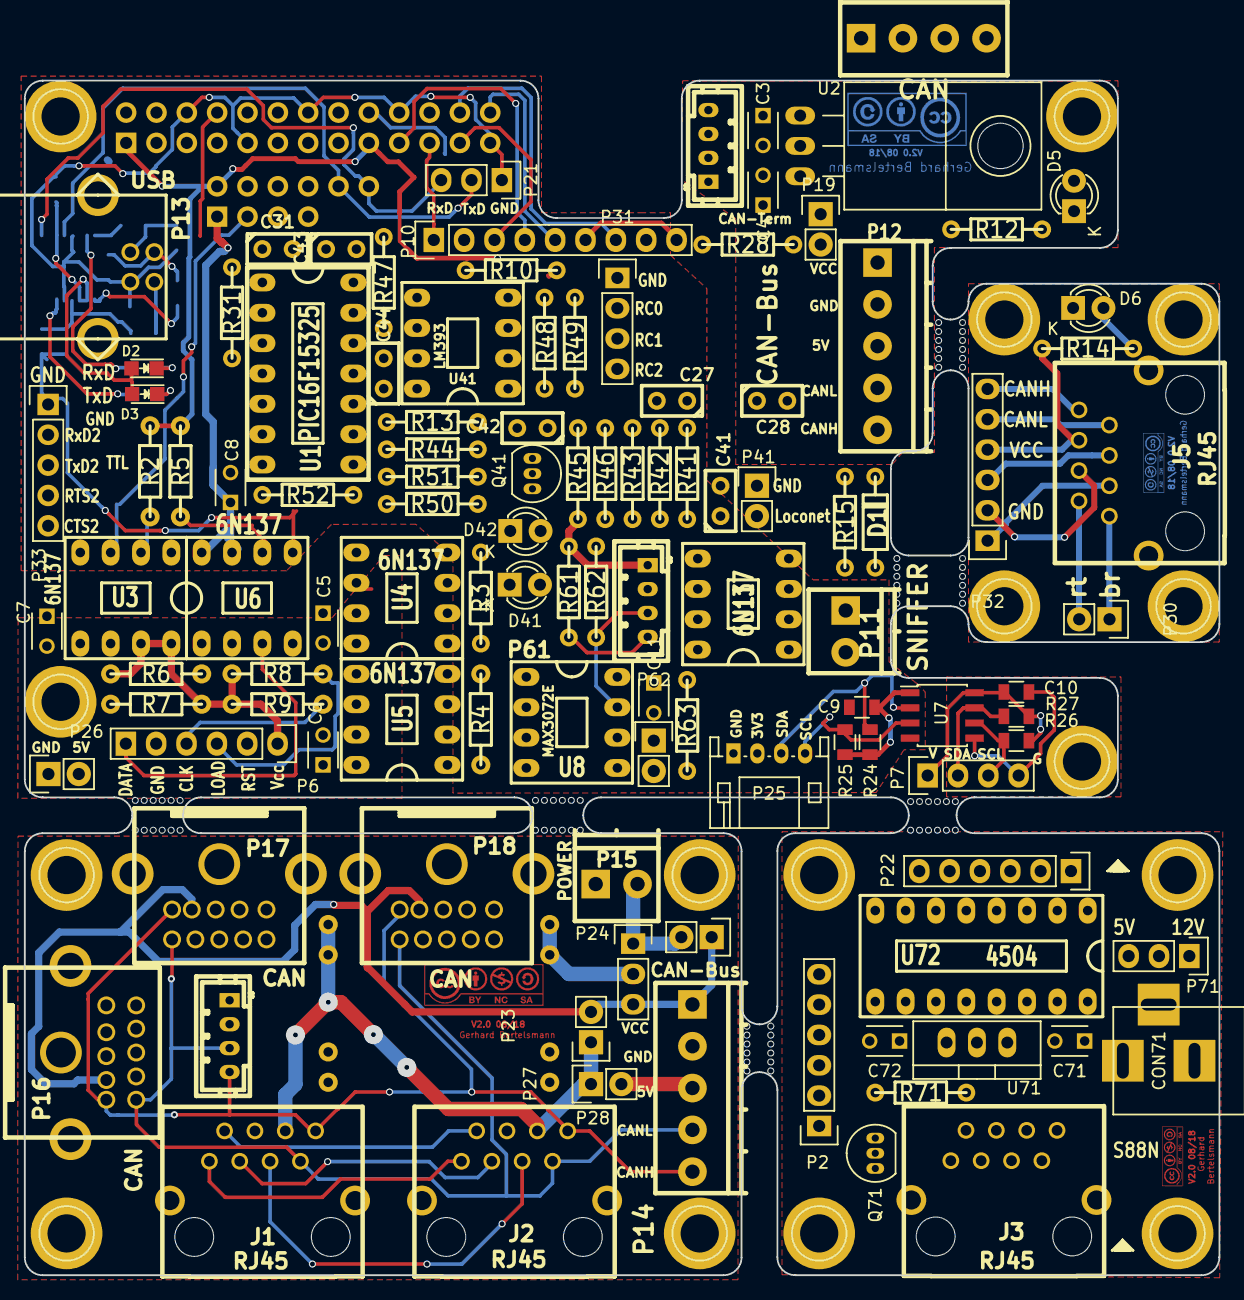
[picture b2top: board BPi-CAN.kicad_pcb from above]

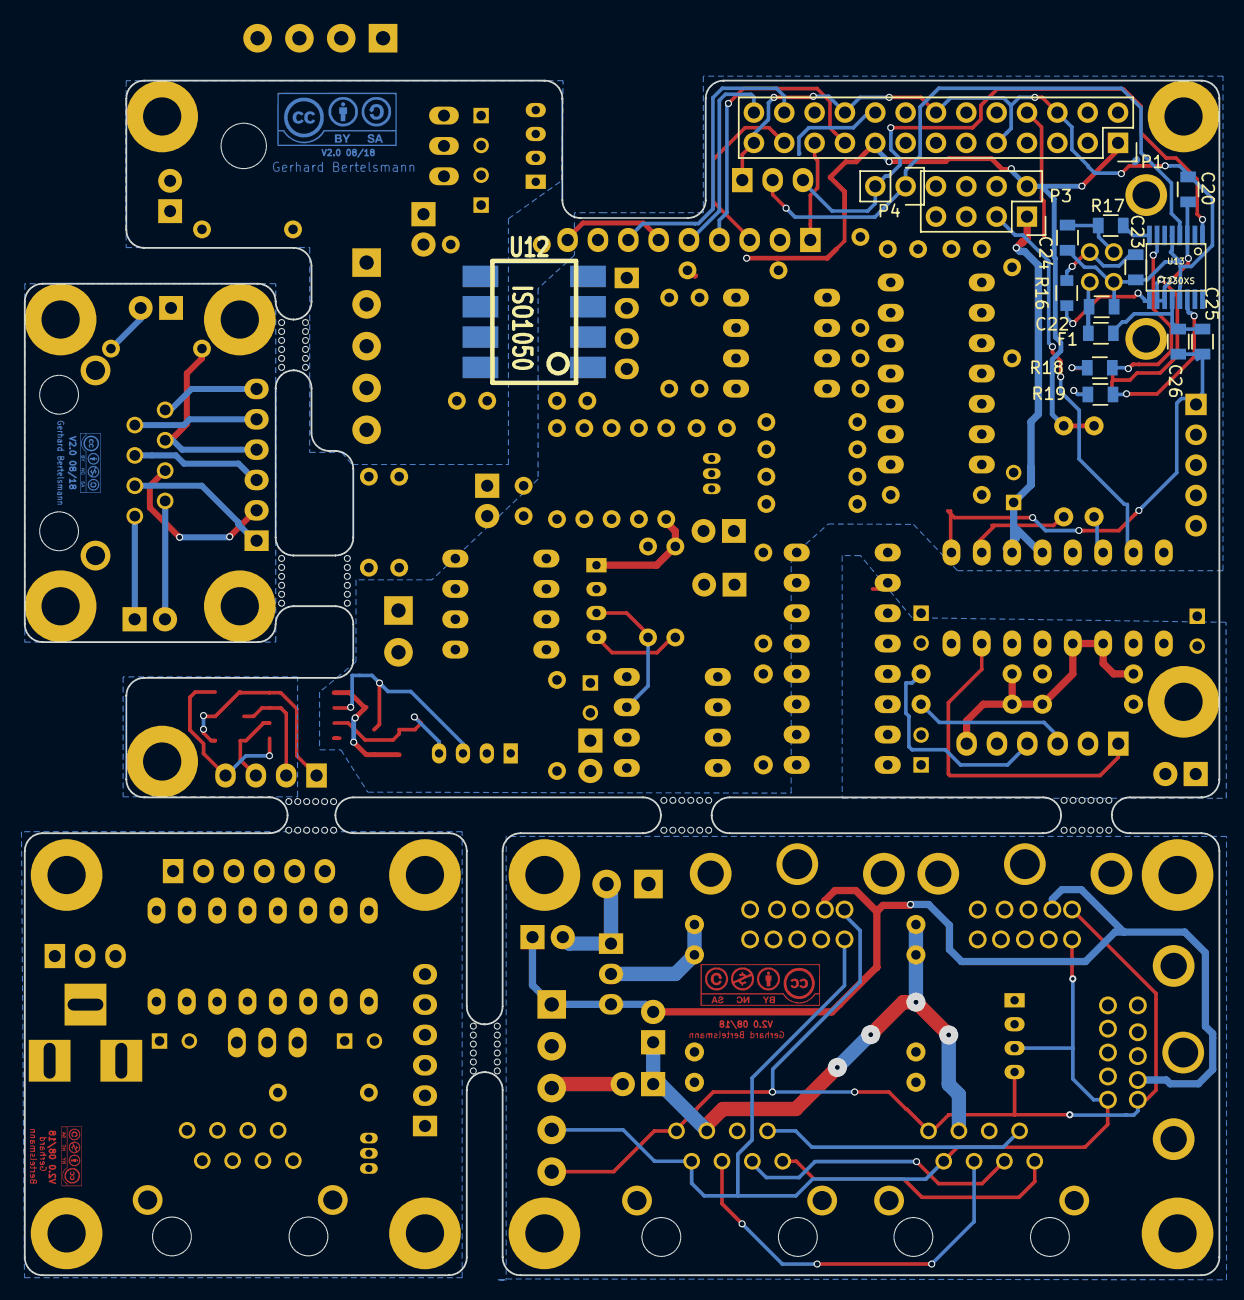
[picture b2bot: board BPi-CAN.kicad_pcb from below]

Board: 2 copper layers, 100.0 x 100.0 mm, 156 parts (16 on the bottom side), 117 nets.

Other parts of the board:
E01, E02, E03, E03#2, E03#3, E04, E05, E05#2, E05#3, E05#4, E05#5, E06: abort edge
R01, R02, R02#2, R02#3, R02#4, R02#5, R03, R04, R05, R06, R07, R08, R010, R011, R012: 1pin
RR08: 1pin
